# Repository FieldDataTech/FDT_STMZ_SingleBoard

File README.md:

# FDT_STMZ_SingleBoard
Single board solution for FDT smart cam using STM32H743ZIT
These are Eagle CADSoft design files for a single board implementation of FDT's smart camera. It is based on a 144-pin STM32H743ZIT processor.

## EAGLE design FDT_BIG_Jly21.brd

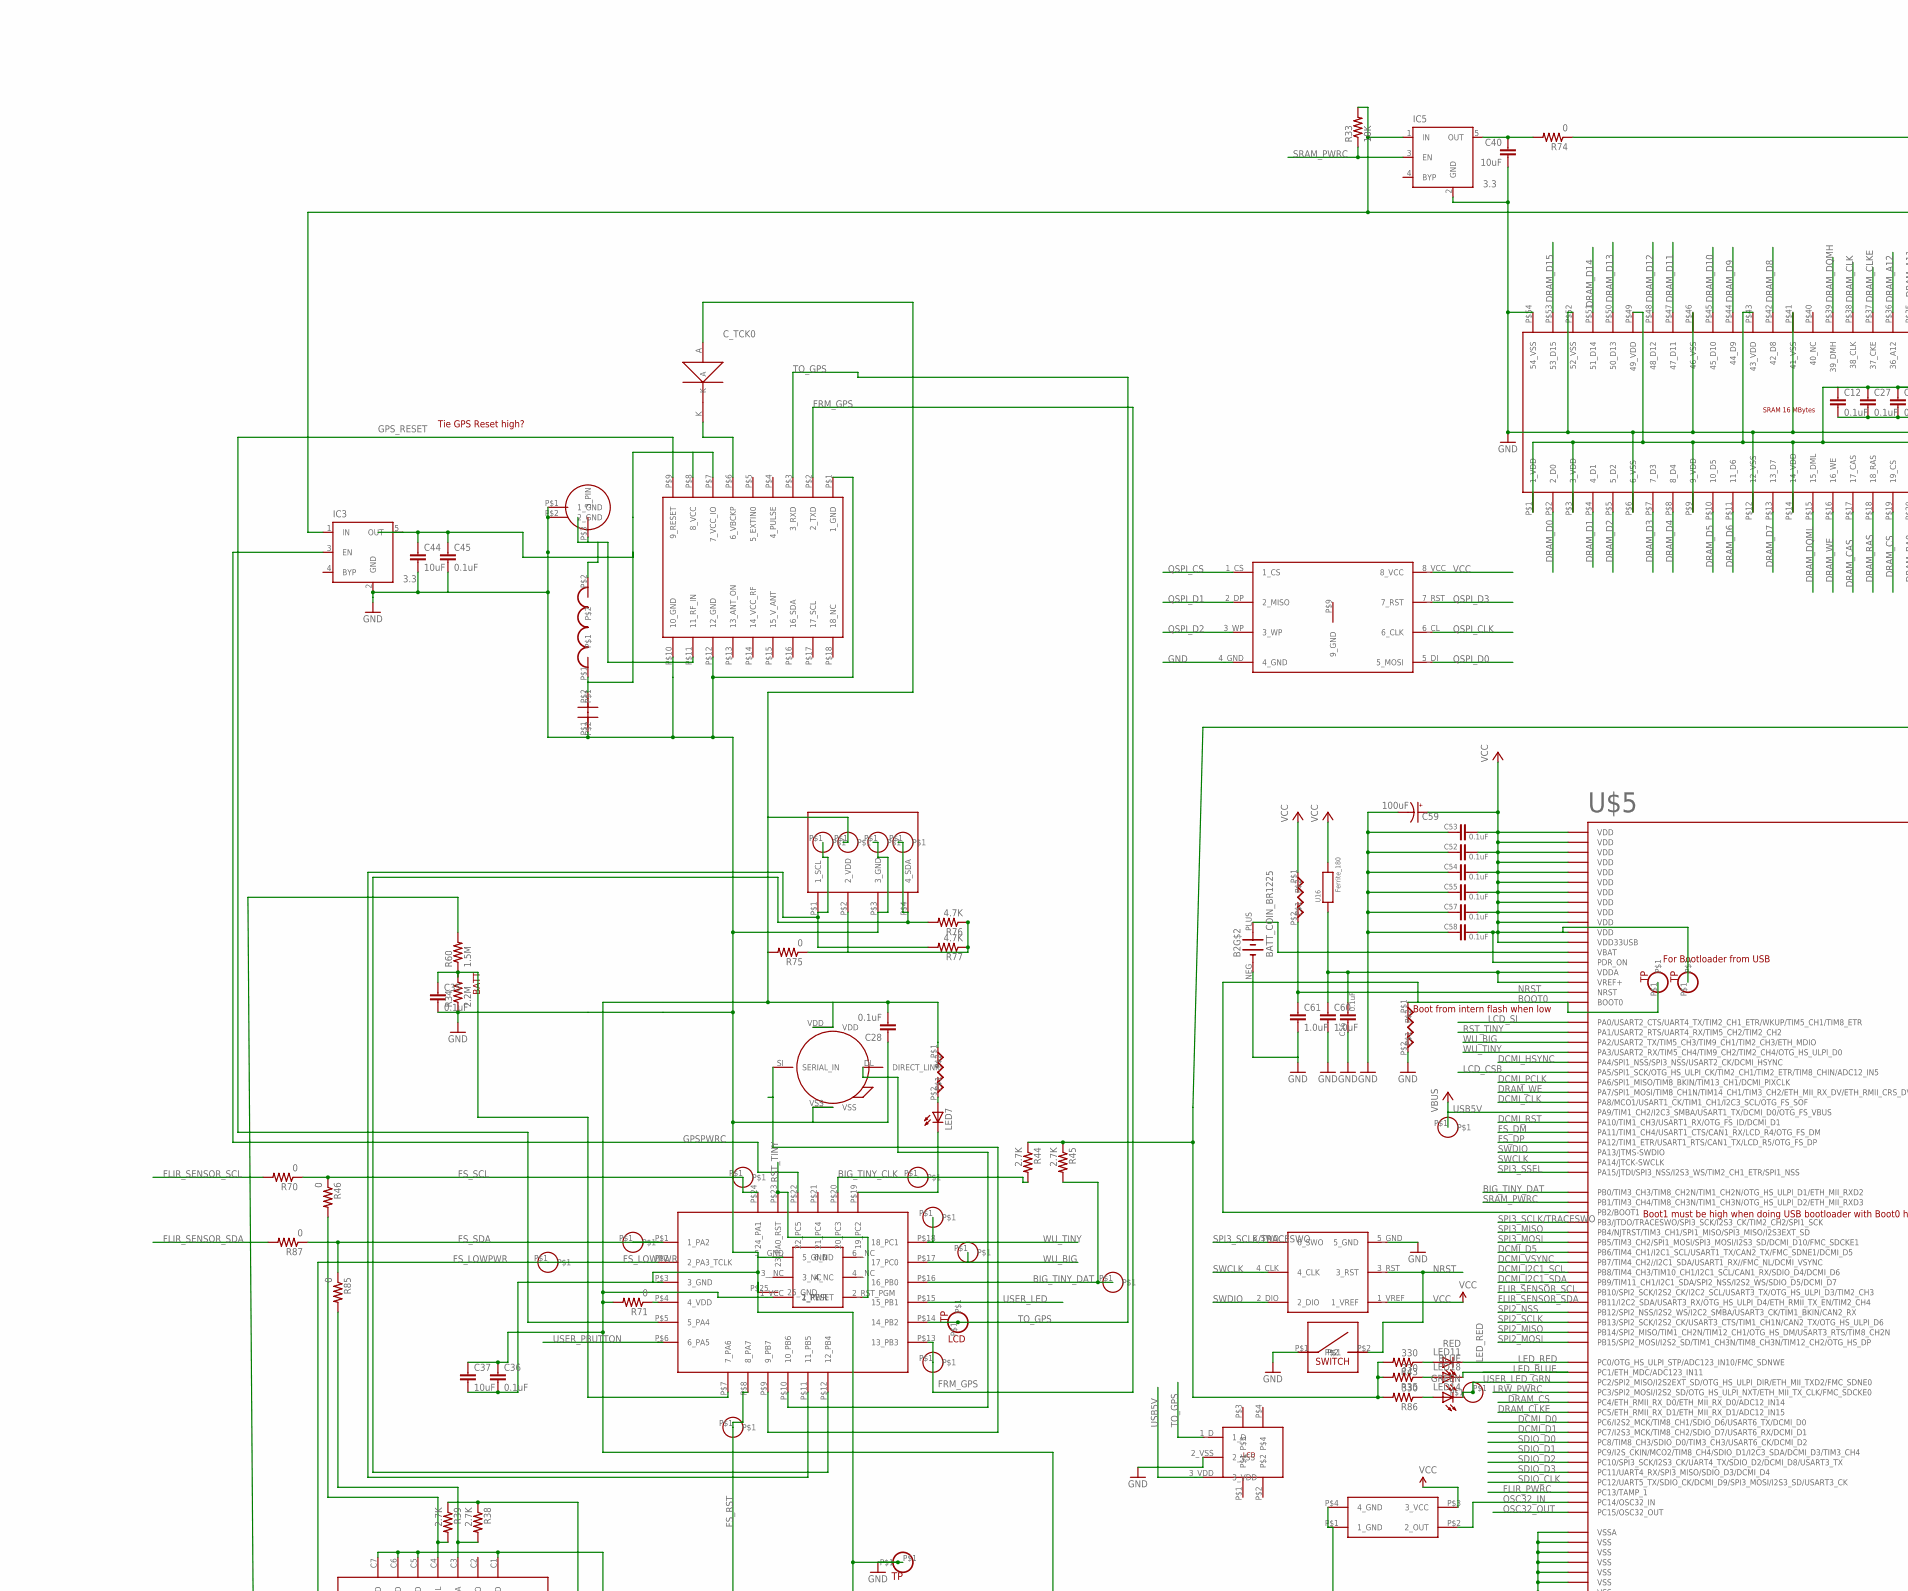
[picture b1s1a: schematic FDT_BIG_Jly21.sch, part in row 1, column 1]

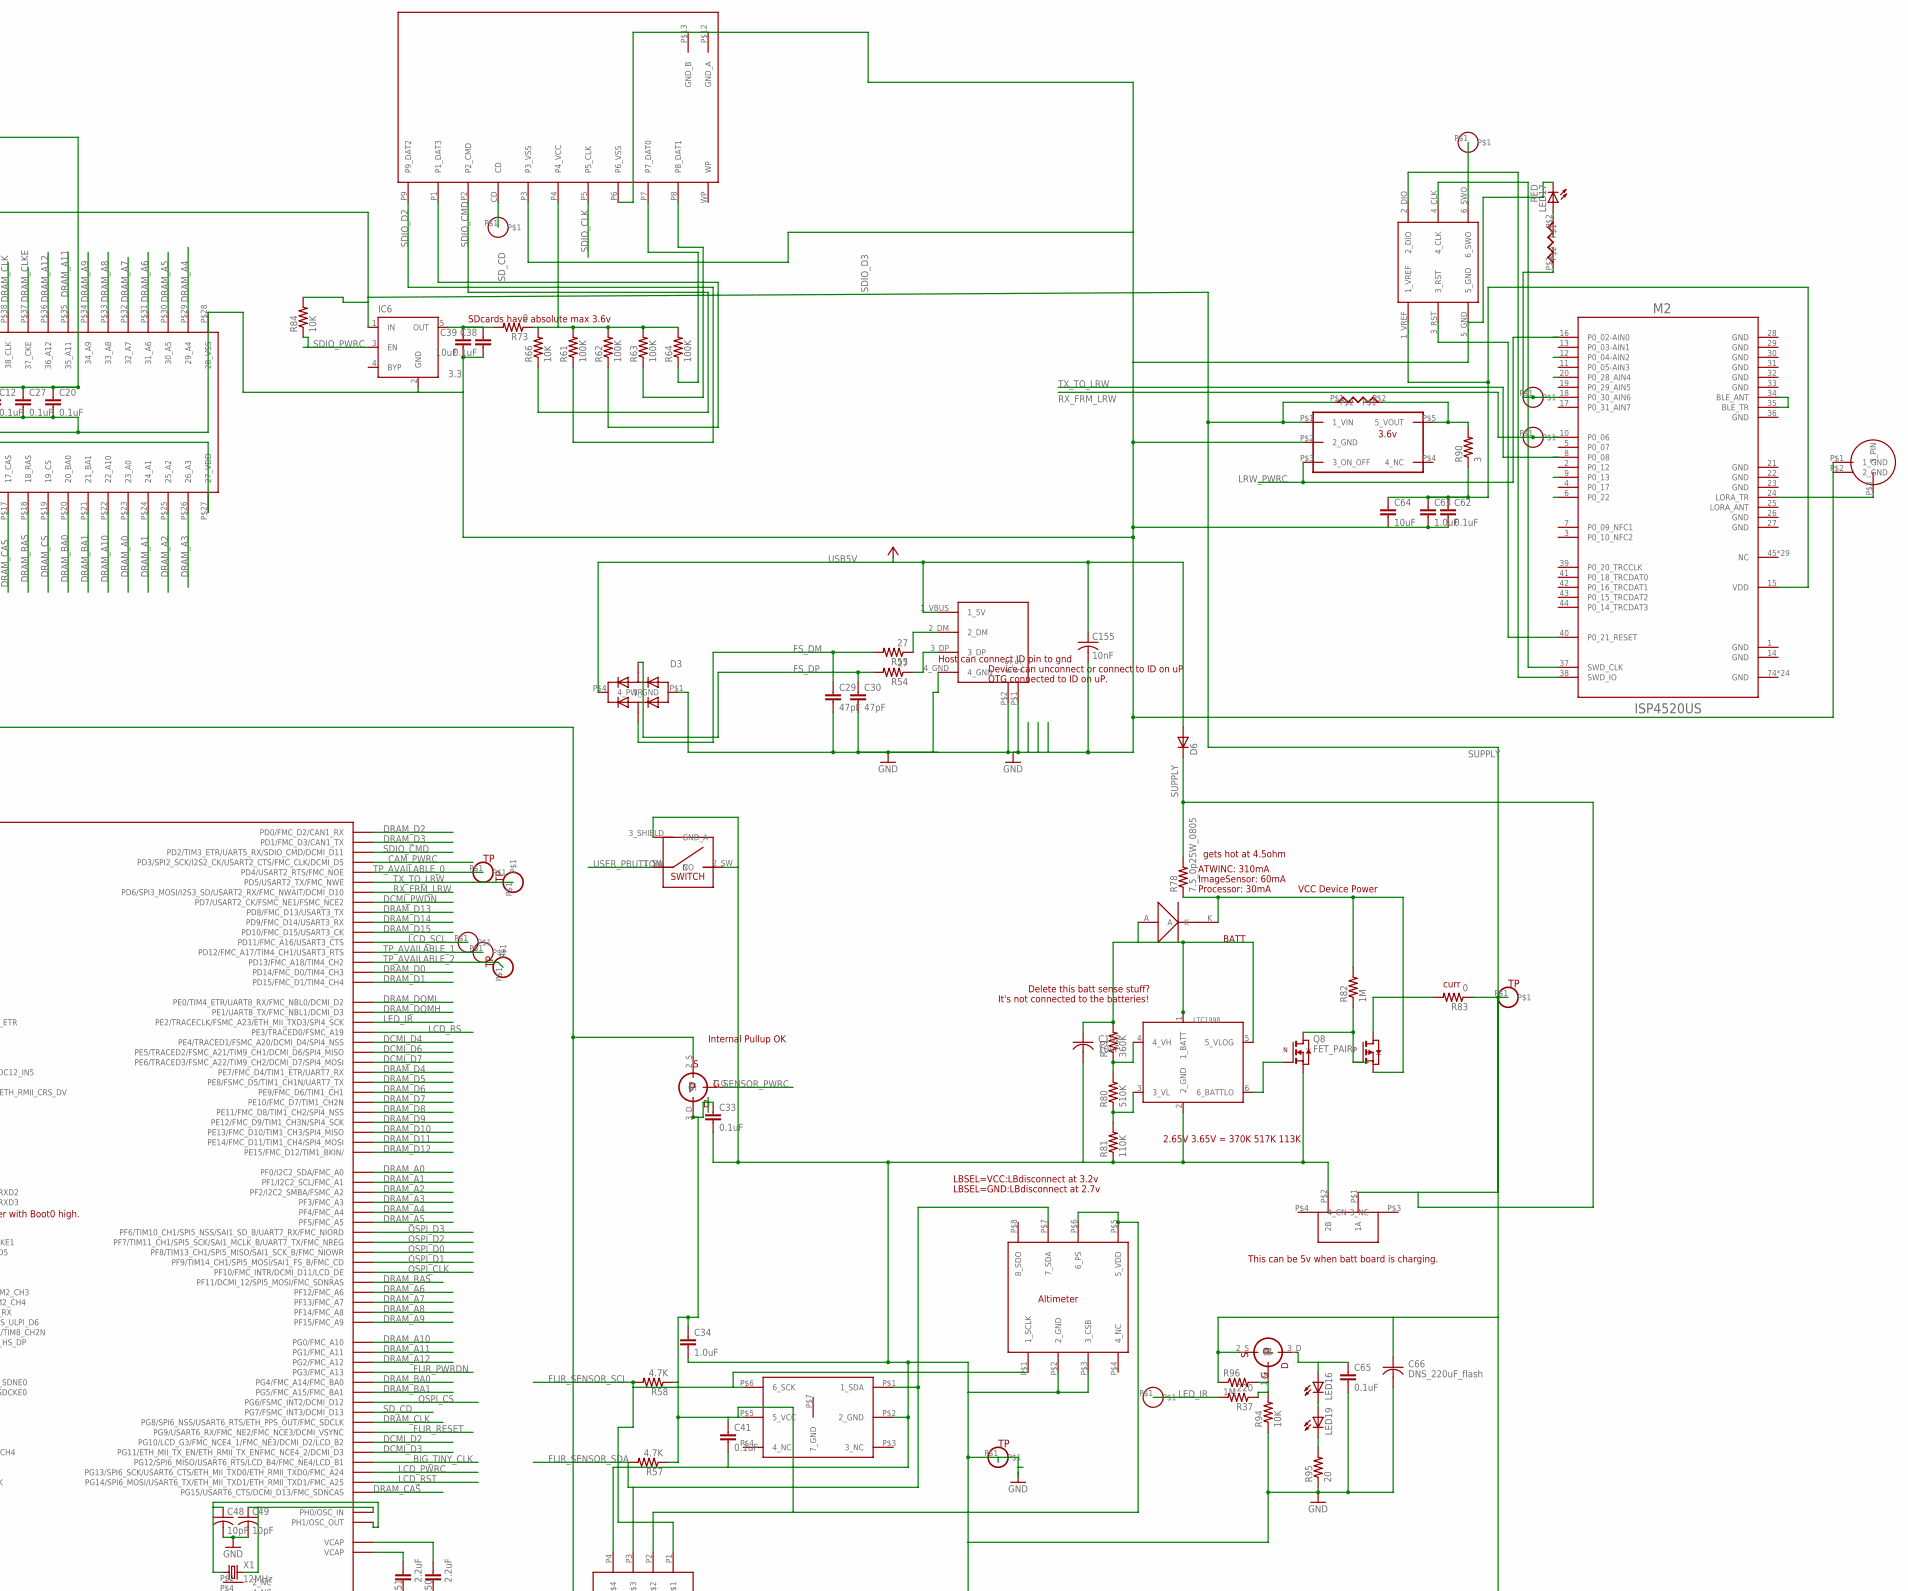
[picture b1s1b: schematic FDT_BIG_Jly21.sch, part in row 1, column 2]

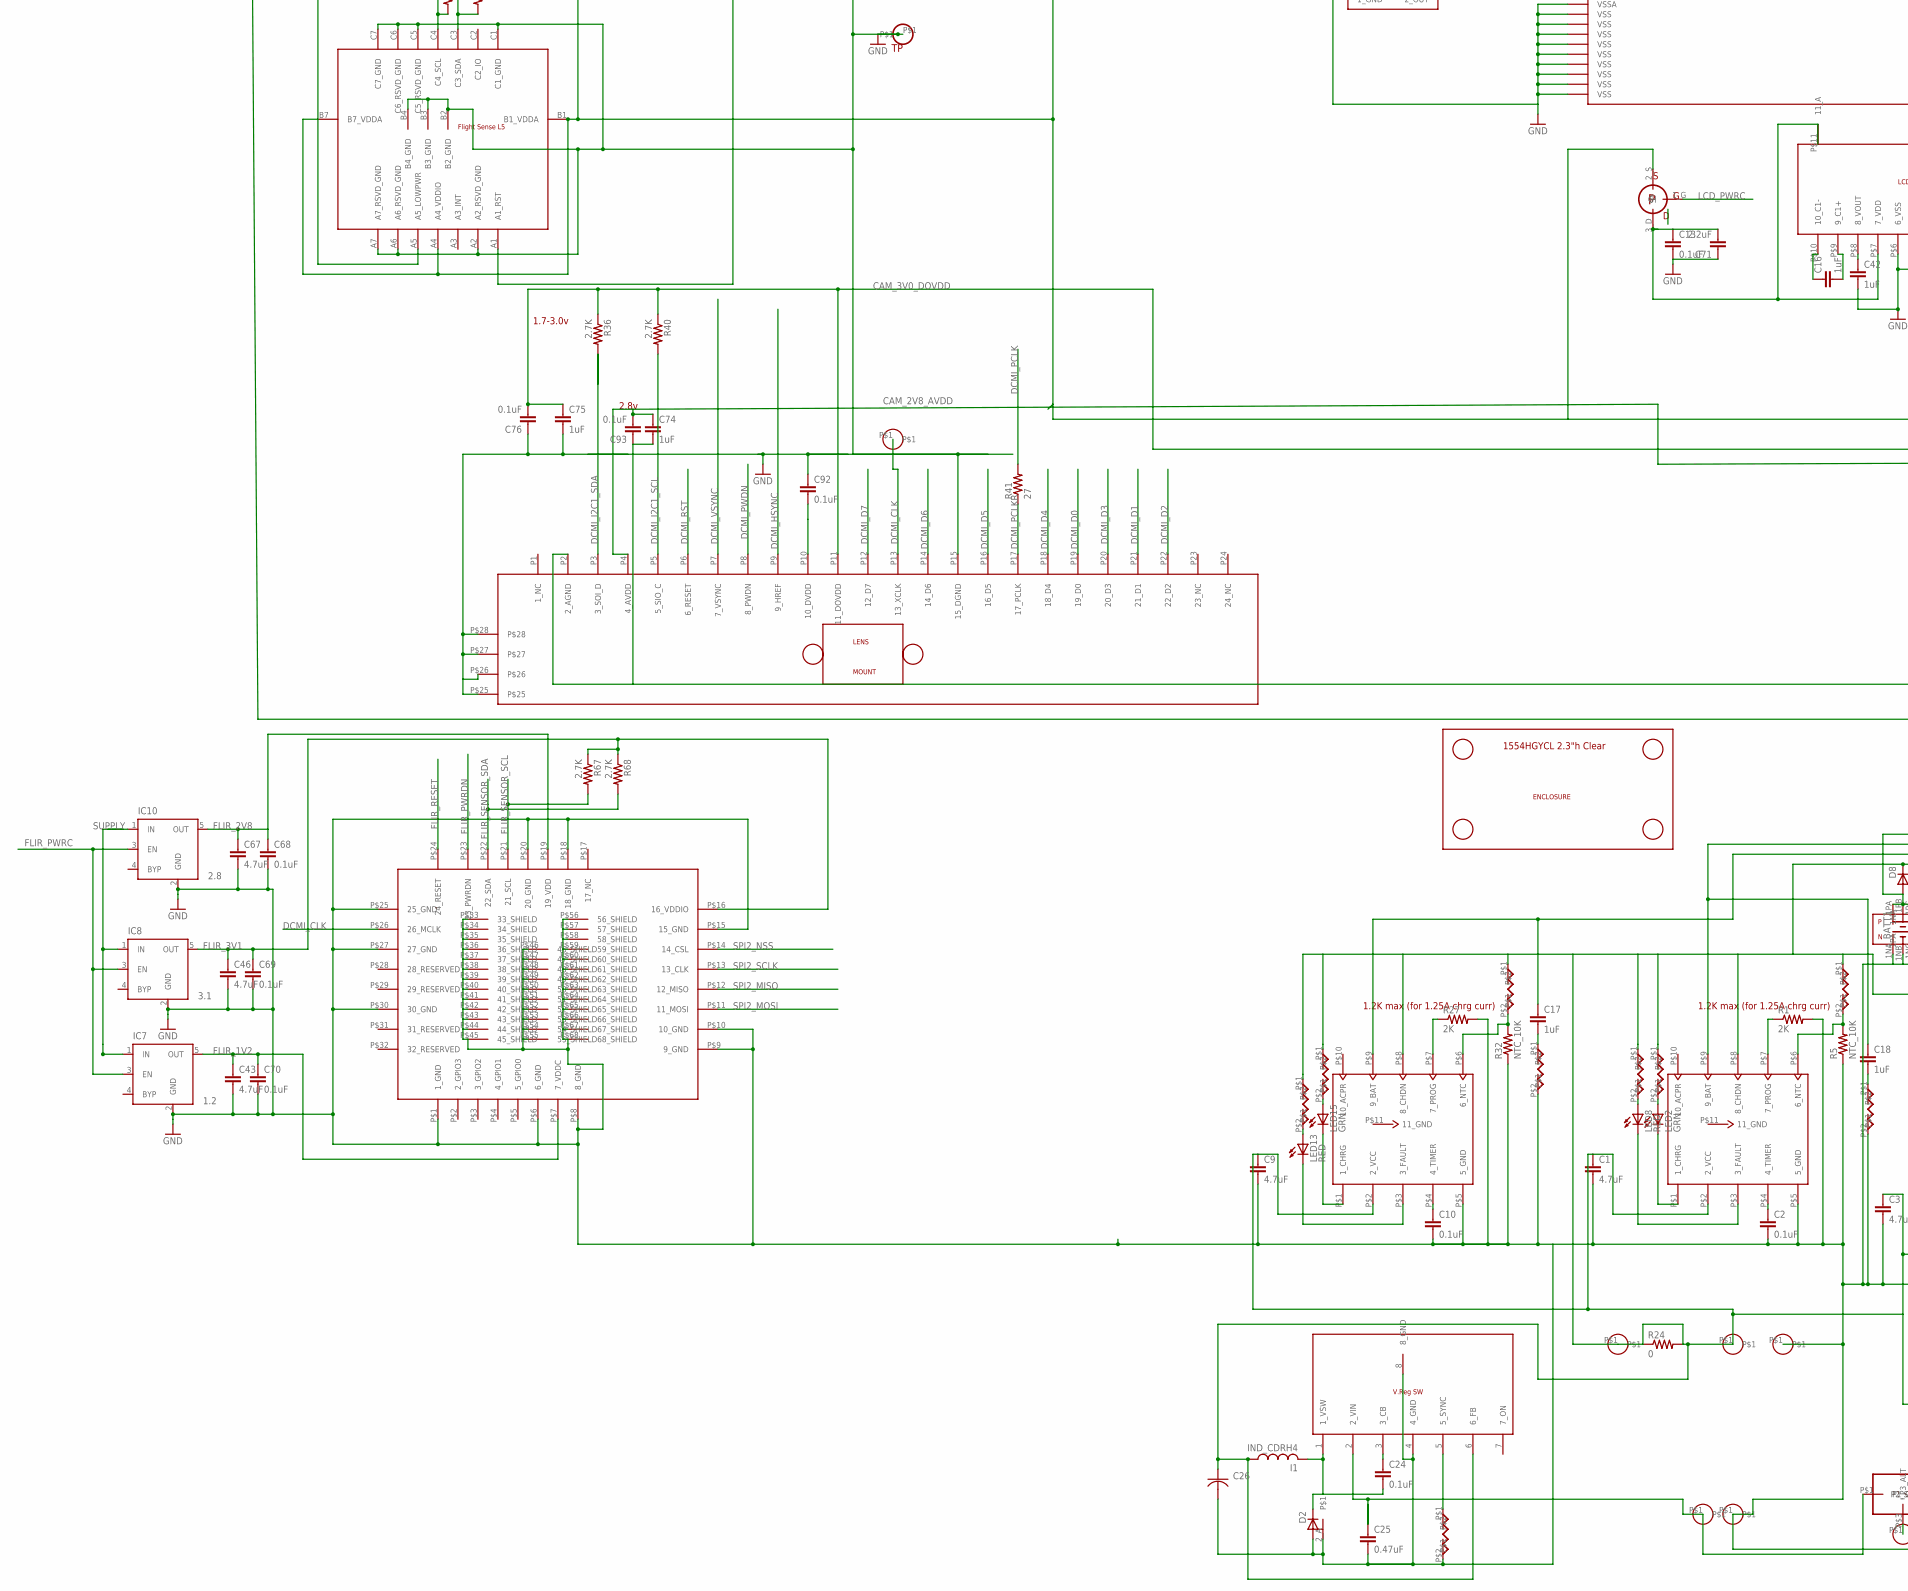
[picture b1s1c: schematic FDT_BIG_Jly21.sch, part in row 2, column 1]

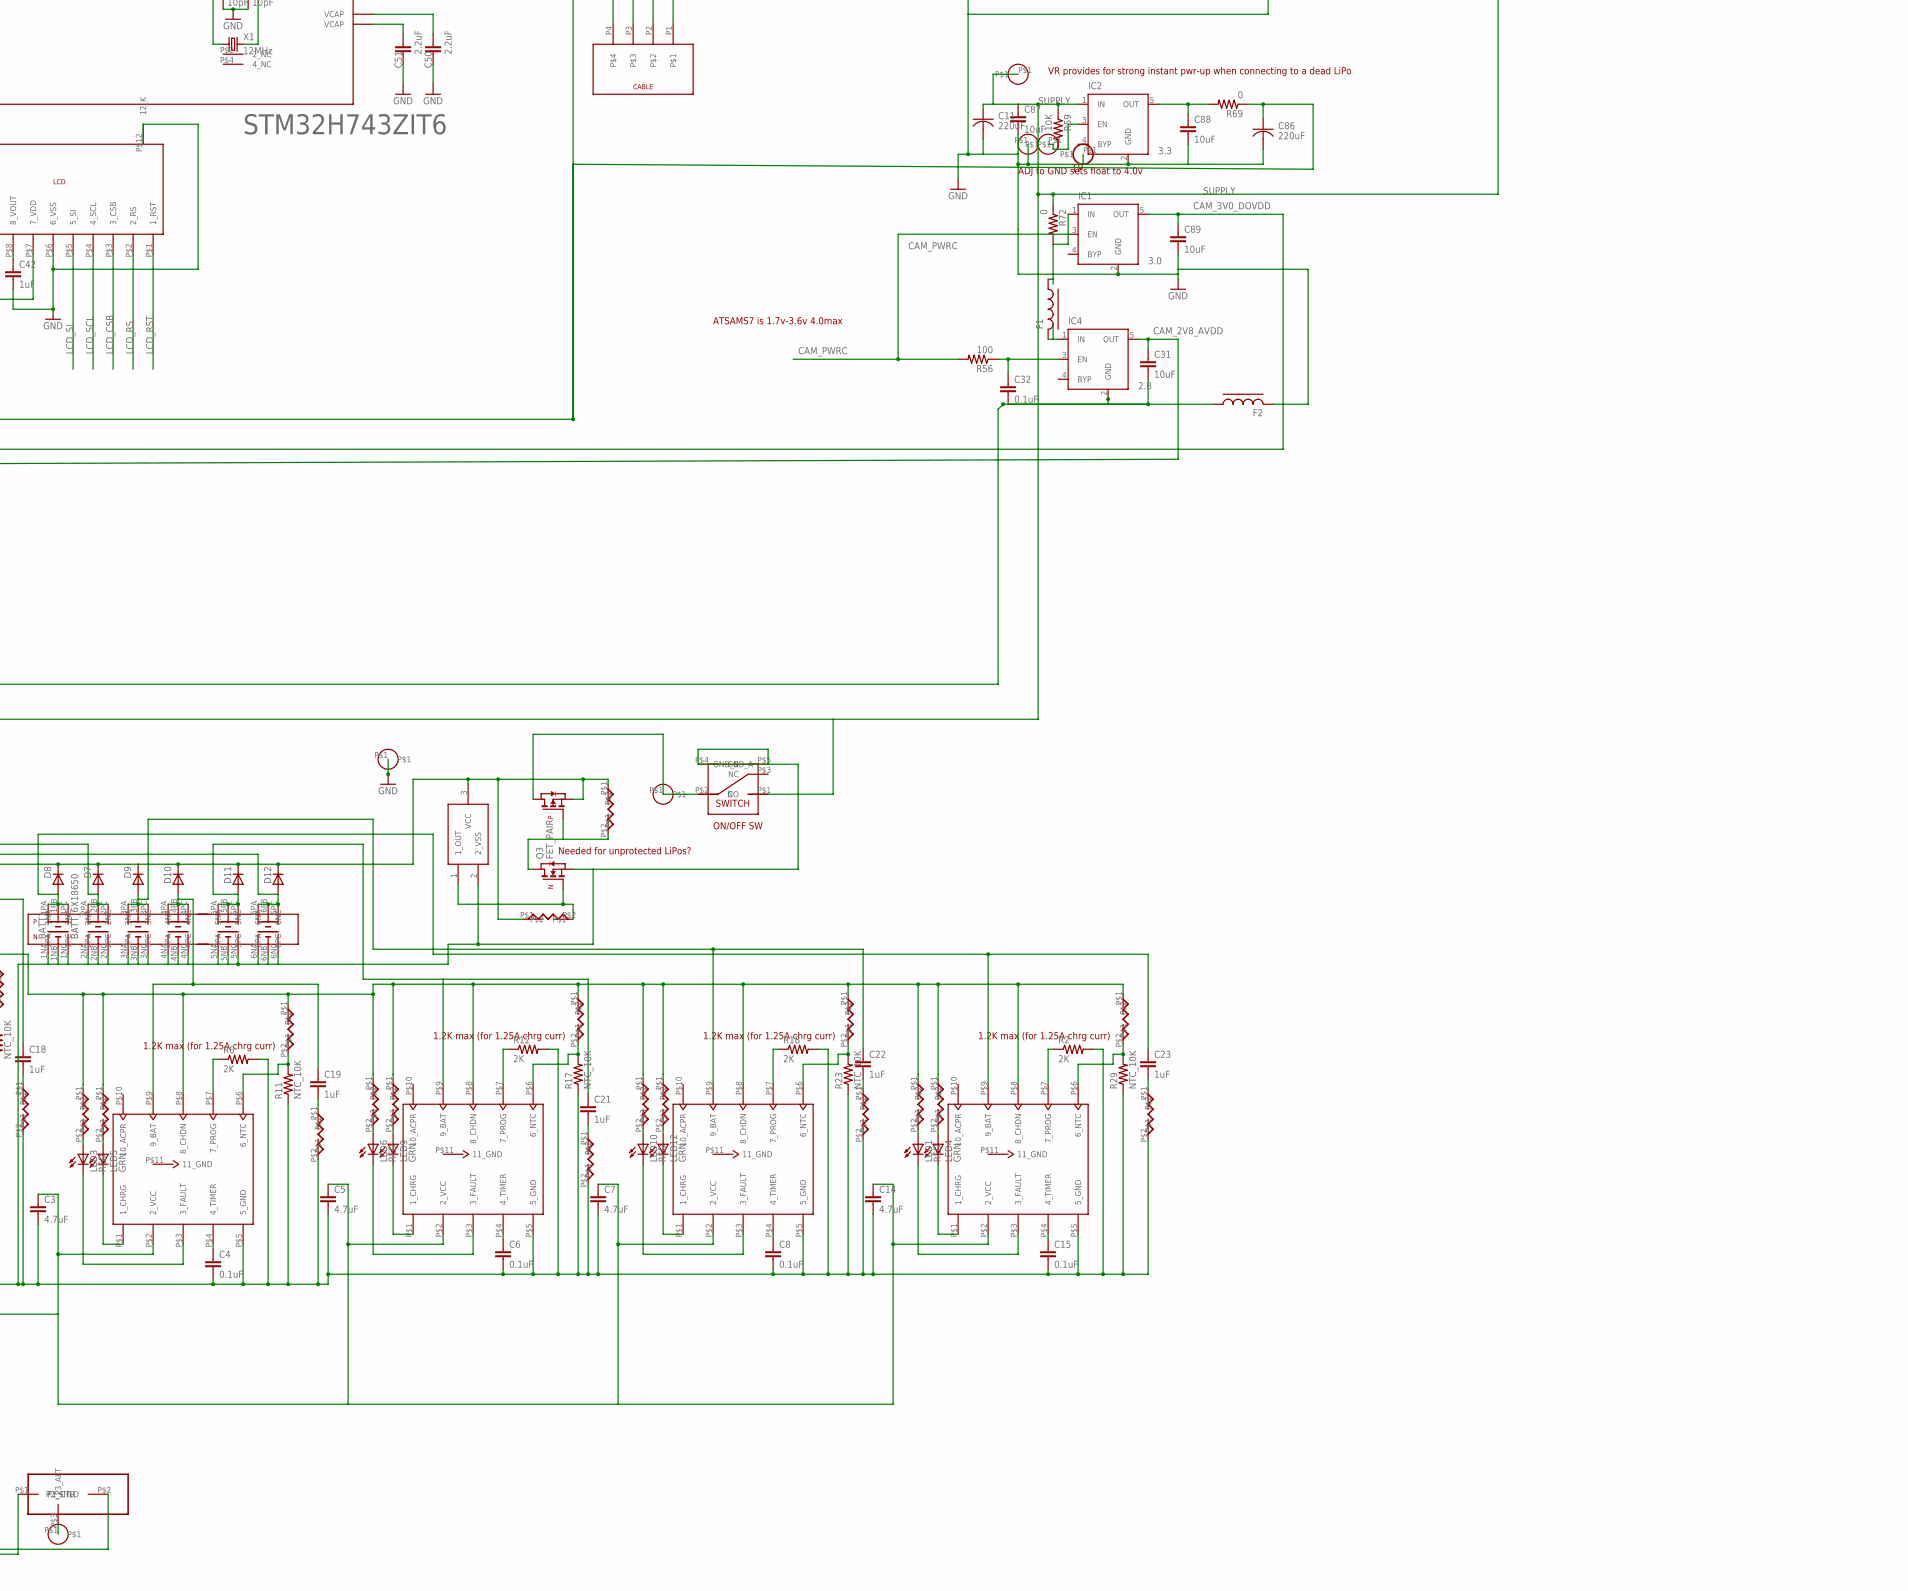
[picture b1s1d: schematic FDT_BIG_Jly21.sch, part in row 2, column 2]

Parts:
B2: BATT_COIN_BR1225
BATT1: BATT_6X18650; BATT_HALFX6
BOX1: ENCL_1554H
C1, C3, C5, C7, C9, C14, C43, C46, C67: 4.7uF; C0603
C2, C4, C6, C8, C10, C12, C13, C15, C20, C24, C27, C28, C32, C33, C35, C36, C38, C41, C45, C62, C65, C68, C69, C70, C76, C92, C93: 0.1uF; C0402
C11, C86: 220uF; C1210K
C16, C17, C18, C19, C21, C22, C23, C42, C74, C75: 1uF; C0603
C25: 0.47uF; C0402
C26: CAP_1210; C1210K
C29, C30: 47pF; C0402
C31, C37, C39, C40, C44, C64, C87, C88, C89: 10uF; C0603
C34, C60, C61, C63: 1.0uF; C0603
C47: 18pF; SMD_0402
C48, C49: 10pF; SMD_0402
C50, C51: 2.2uF; 0603-CAP
C52, C53, C54, C55, C56, C57, C58: 0.1uF; 0402-CAP
C59: 100uF; EIA3216
C66: DNS_220uF_flash; C1210K
C71: 2.2uF; C0603
C102: 10uF; C0805ELEC
C155: 10nF; SMD_0402
D2: DIODE_BIG
D3: ESD_SM; TVSDIODE
D4, D5: DIO_SCH; SOD323
D6, D7, D8, D9, D10, D11, D12: DIODE_SCHTKY; SOD323
F1, F2: FERRITE_0603; R0603
G1, G2: GPS_ANT; GPS_ANTE
I1: IND_CDRH4; IND_CDRH4D
IC1: 3.0; SOT23-5
IC2, IC3, IC5, IC6: 3.3; SOT23-5
IC4, IC10: 2.8; SOT23-5
IC7: 1.2; SOT23-5
IC8: 3.1; SOT23-5
IR1: FLIR_LEPTOP_SOCKET; FLIR_SOCKET
J2: CONN_FPC_24P; CONN_FPC_24PIN
J3: USB_B_SMT_HORIZ
J4, J8: HDR_SEGER_6P; HDR_SEGGER_6P
J5: HDR_PGM_TINY_SMT
J6: CONN_4PCABLE_VERT; CONN_4PCABLE
J7: CONN_2PCABLE_SMT
J9: PWR_JAC4
L5: 100nH; SMD_IND
LCD1: LCD_NHD_3PIN; LCD_NHD_3PINS
LED1, LED3, LED6, LED8, LED10, LED11, LED13, LED17: RED; CHIP-LED0603
LED2, LED4, LED5, LED9, LED12, LED15: GRN; CHIP-LED0603
LED7: LEDCHIP-LED0603; CHIP-LED0603
LED14: GREEN; LED_RA_SM
LED16, LED19: LED5MM
LED18: BLUE; LED_RA_SM
LM2: LENS_MOUNT_CMT107
M2: ISP4520US; ISP4520-LGA-QFN74-9.8X17.2X1.7MM
PIR2: PIR_DUAL_4P; PIR_4P
Q1, Q2, Q5: MOSFET_P; SOT23_PFET
Q3, Q8: FET_PAIR; SSOT6
R1, R2, R6, R12, R18, R27: 2K; SMD_0402
R3, R7, R8, R9, R13, R14, R15, R19, R21, R28, R30, R53, R65, R92: 1K; SMD_0402
R4, R10, R16, R20, R22, R31: 4k; SMD_0402
R5, R11, R17, R23, R29, R32: NTC_10K; R0603
R24: 0; SMD_0402
R25, R26: 1M; SMD_0402
R33, R59, R66, R84, R94: 10K; R0402
R34: 2.2M; R0402
R35, R43, R86: 330; R0402
R36, R38, R39, R40, R44, R45, R67, R68: 2.7K; SMD_0402
R37: 220; R0402
R41: 27; SMD_0402
R42: 330; SMD_0402
R46, R69, R70, R71, R72, R73, R74, R75, R83, R85, R87: 0; R0402
R47, R48, R49, R50, R51, R52: 1ohm; SMD_0402
R54, R55: 27; R0402
R56: 100; R0402
R57, R58, R76, R77: 4.7K; R0402
R60: 1.5M; R0402
R61, R62, R63, R64: 100K; R0402
R78: 7.5_0p25W_0805; M0805
R79: 360K; R0402
R80: 510K; R0402
R81: 110K; R0402
R82, R96: 1M; R0402
R88, R89: 10K; SMD_0402
R90: 3; R0402
R91: DNS_0; SMD_0402
R95: 20; R0402
SD1: SD_CARD
SW1: SWITH_NO; SW_SQ
SW2: SWITCH_TOG_RA; SW_TOG_RA
SW3: SW_PBUTTON_RA
T1, T2, T3, T4, T5, T6, T7, T8, T12, T13: TESTP_SM
TP1, TP2, TP3, TP4, TP5, TP6, TP7, TP14, TP16, TP17, TP24: TP_THSM2
TP8, TP9, TP10, TP18, TP19, TP20, TP21, TP22, TP23, TP25, TP26, TP27, TP29, TP31, TP32, TP41, TP42, TP43, TP46: TP_SMT
TP11, TP12, TP13, TP15: TP_THSM
U1, U2, U3, U4, U5, U10: LTC4053
U6: HUMIDITY_A
U7: VOLT_SUPR; TO236
U8: FLIGHTSENSE_L5; FLIGHT_SENSE_L5
U11: VREG_SW_LM2677; TO263-7
U12: SRAM_16M_2X16; TSOP_54
U13: ALS
U15: UBLOX_M8
U16: Ferrite_180; 0402-CAP
U17: FLASH_SPI; WSON_8
U18: 3.6v; SOT_235B
U19: LTC1998; SOT23-6L
U20: ALTIMETER_TEC
U24: ATTINY_817_QFN; QFN24
U$1: LCD_3V_SMALL
U$5: STM32H743ZIT6; LQFP144@1
X1: 12MHz; XTAL_SMALL
X2: TCXO_32K_BGA

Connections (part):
5VREG_OUT: C1.1, C3.1, C5.1, C7.1, C9.1, C14.1, C26.1 (1P), D7.1_K (K), D8.1_K (K), D9.1_K (K), D10.1_K (K), D11.1_K (K), D12.1_K (K), I1.P$3 (1), Q3.2 (P_S), R3.P$1, R4.P$1, R7.P$1, R8.P$1, R9.P$1, R10.P$1, R13.P$1, R14.P$1, R15.P$1, R16.P$1, R19.P$1, R20.P$1, R21.P$1, R22.P$1, R24.P$1 (1), R24.P$2 (2), R25.P$1, R26.P$1, R28.P$1, R30.P$1, R31.P$1, R65.P$1, TP2.P$1, TP4.P$1, U1.P$2 (2_VCC), U1.P$8 (8_CHDN), U2.P$2 (2_VCC), U2.P$8 (8_CHDN), U3.P$2 (2_VCC), U3.P$8 (8_CHDN), U4.P$2 (2_VCC), U4.P$8 (8_CHDN), U5.P$2 (2_VCC), U5.P$8 (8_CHDN), U7.3 (VCC), U10.P$2 (2_VCC), U10.P$8 (8_CHDN), U11.6 (6_FB)
AGND: C31.2, C32.2, C74.2, C93.1, F2.1, IC4.2 (GND), J2.P2 (2_AGND)
BATT: C102.1P, D5.A, R79.2, U19.1 (1_BATT), U19.5 (5_VLOG)
BIG_TINY_CLK: R44.P$2 (2), TP29.P$1, U24.P$20 (20_PC3), U$5.127 (PG12/SPI6_MISO/USART6_RTS/LCD_B4/FMC_NE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)
BIG_TINY_DAT: R45.P$2 (2), TP27.P$1, U24.P$16 (16_PB0), U$5.46 (PB0/TIM3_CH3/TIM8_CH2N/TIM1_CH2N/OTG_HS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)
BOOT0: R89.P$1, T7.P$1, U$5.48 (PB2/BOOT1), U$5.138 (BOOT0)
CAM_2V8_AVDD: C31.1, C74.1, C93.2, IC4.5 (OUT), J2.P4 (4_AVDD)
CAM_3V0_DOVDD: C75.1, C76.2, C89.1, IC1.5 (OUT), J2.P11 (11_DOVDD), R36.P$1 (1), R40.P$1 (1)
CAM_PWRC: IC1.3 (EN), R56.2, U$5.117 (PD3/SPI2_SCK/I2S2_CK/USART2_CTS/FMC_CLK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)
DCMI_CLK: IR1.P$26 (26_MCLK), J2.P13 (13_XCLK), TP25.P$1, U$5.100 (PA8/MCO1/USART1_CK/TIM1_CH1/I2C3_SCL/OT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)
DCMI_D0: J2.P19 (19_D0), U$5.96 (PC6/I2S2_MCK/TIM8_CH1/SDIO_D6/USART6_TX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)
DCMI_D1: J2.P21 (21_D1), U$5.97 (PC7/I2S3_MCK/TIM8_CH2/SDIO_D7/USART6_RX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)
DCMI_D2: J2.P22 (22_D2), U$5.125 (PG10/LCD_G3/FMC_NCE4_1/FMC_NE3/DCMI_D2/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)
DCMI_D3: J2.P20 (20_D3), U$5.126 (PG11/ETH_MII_TX_EN/ETH_RMII_TX_ENFMC_NC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)
DCMI_D4: J2.P18 (18_D4), U$5.3 (PE4/TRACED1/FSMC_A20/DCMI_D4/SPI4_NSS)
DCMI_D5: J2.P16 (16_D5), U$5.136 (PB6/TIM4_CH1/I2C1_SCL/USART1_TX/CAN2_TX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)
DCMI_D6: J2.P14 (14_D6), U$5.4 (PE5/TRACED2/FSMC_A21/TIM9_CH1/DCMI_D6/S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)
DCMI_D7: J2.P12 (12_D7), U$5.5 (PE6/TRACED3/FSMC_A22/TIM9_CH2/DCMI_D7/S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)
DCMI_HSYNC: J2.P9 (9_HREF), U$5.40 (PA4/SPI1_NSS/SPI3_NSS/USART2_CK/DCMI_HS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)
DCMI_I2C1_SCL: J2.P5 (5_SIO_C), R40.P$2 (2), U$5.139 (PB8/TIM4_CH3/TIM10_CH1/I2C1_SCL/CAN1_RX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)
DCMI_I2C1_SDA: J2.P3 (3_SOI_D), R36.P$2 (2), U$5.140 (PB9/TIM11_CH1/I2C1_SDA/SPI2_NSS/I2S2_WS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)
DCMI_PCLK: R41.P$2 (2), U$5.42 (PA6/SPI1_MISO/TIM8_BKIN/TIM13_CH1/DCMI_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)
DCMI_PCLKR: J2.P17 (17_PCLK), R41.P$1 (1)
DCMI_PWDN: J2.P8 (8_PWDN), U$5.123 (PD7/USART2_CK/FSMC_NE1/FSMC_NCE2)
DCMI_RST: J2.P6 (6_RESET), U$5.102 (PA10/TIM1_CH3/USART1_RX/OTG_FS_ID/DCMI_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)
DCMI_VSYNC: J2.P7 (7_VSYNC), U$5.137 (PB7/TIM4_CH2//I2C1_SDA/USART1_RX//FMC_N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)
DISABLE_PWR: IC2.3 (EN), R59.2, TP17.P$1
DRAM_A0: U12.P$23 (23_A0), U$5.10 (PF0/I2C2_SDA/FMC_A0)
DRAM_A1: U12.P$24 (24_A1), U$5.11 (PF1/I2C2_SCL/FMC_A1)
DRAM_A2: U12.P$25 (25_A2), U$5.12 (PF2/I2C2_SMBA/FSMC_A2)
DRAM_A3: U12.P$26 (26_A3), U$5.13 (PF3/FMC_A3)
DRAM_A4: U12.P$29 (29_A4), U$5.14 (PF4/FMC_A4)
DRAM_A5: U12.P$30 (30_A5), U$5.15 (PF5/FMC_A5)
DRAM_A6: U12.P$31 (31_A6), U$5.50 (PF12/FMC_A6)
DRAM_A7: U12.P$32 (32_A7), U$5.53 (PF13/FMC_A7)
DRAM_A8: U12.P$33 (33_A8), U$5.54 (PF14/FMC_A8)
DRAM_A9: U12.P$34 (34_A9), U$5.55 (PF15/FMC_A9)
DRAM_A10: U12.P$22 (22_A10), U$5.56 (PG0/FMC_A10)
DRAM_A11: U12.P$35 (35_A11), U$5.57 (PG1/FMC_A11)
DRAM_A12: U12.P$36 (36_A12), U$5.87 (PG2/FMC_A12)
DRAM_BA0: U12.P$20 (20_BA0), U$5.89 (PG4/FMC_A14/FMC_BA0)
DRAM_BA1: U12.P$21 (21_BA1), U$5.90 (PG5/FMC_A15/FMC_BA1)
DRAM_CAS: U12.P$17 (17_CAS), U$5.132 (PG15/USART6_CTS/DCMI_D13/FMC_SDNCAS)
DRAM_CLK: U12.P$38 (38_CLK), U$5.93 (PG8/SPI6_NSS/USART6_RTS/ETH_PPS_OUT/FMC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)
DRAM_CLKE: U12.P$37 (37_CKE), U$5.45 (PC5/ETH_RMII_RX_D1/ETH_MII_RX_D1/ADC12_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)
DRAM_CS: U12.P$19 (19_CS), U$5.44 (PC4/ETH_RMII_RX_D0/ETH_MII_RX_D0/ADC12_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)
DRAM_D0: U12.P$2 (2_D0), U$5.85 (PD14/FMC_D0/TIM4_CH3)
DRAM_D1: U12.P$4 (4_D1), U$5.86 (PD15/FMC_D1/TIM4_CH4)
DRAM_D2: U12.P$5 (5_D2), U$5.114 (PD0/FMC_D2/CAN1_RX)
DRAM_D3: U12.P$7 (7_D3), U$5.115 (PD1/FMC_D3/CAN1_TX)
DRAM_D4: U12.P$8 (8_D4), U$5.58 (PE7/FMC_D4/TIM1_ETR/UART7_RX)
DRAM_D5: U12.P$10 (10_D5), U$5.59 (PE8/FSMC_D5/TIM1_CH1N/UART7_TX)
DRAM_D6: U12.P$11 (11_D6), U$5.60 (PE9/FMC_D6/TIM1_CH1)
DRAM_D7: U12.P$13 (13_D7), U$5.63 (PE10/FMC_D7/TIM1_CH2N)
DRAM_D8: U12.P$42 (42_D8), U$5.64 (PE11/FMC_D8/TIM1_CH2/SPI4_NSS)
DRAM_D9: U12.P$44 (44_D9), U$5.65 (PE12/FMC_D9/TIM1_CH3N/SPI4_SCK)
DRAM_D10: U12.P$45 (45_D10), U$5.66 (PE13/FMC_D10/TIM1_CH3/SPI4_MISO)
DRAM_D11: U12.P$47 (47_D11), U$5.67 (PE14/FMC_D11/TIM1_CH4/SPI4_MOSI)
DRAM_D12: U12.P$48 (48_D12), U$5.68 (PE15/FMC_D12/TIM1_BKIN/)
DRAM_D13: U12.P$50 (50_D13), U$5.77 (PD8/FMC_D13/USART3_TX)
DRAM_D14: U12.P$51 (51_D14), U$5.78 (PD9/FMC_D14/USART3_RX)
DRAM_D15: U12.P$53 (53_D15), U$5.79 (PD10/FMC_D15/USART3_CK)
DRAM_DQMH: U12.P$39 (39_DMH), U$5.142 (PE1/UART8_TX/FMC_NBL1/DCMI_D3)
DRAM_DQML: U12.P$15 (15_DML), U$5.141 (PE0/TIM4_ETR/UART8_RX/FMC_NBL0/DCMI_D2)
DRAM_RAS: U12.P$18 (18_RAS), U$5.49 (PF11/DCMI_12/SPI5_MOSI/FMC_SDNRAS)
DRAM_WE: U12.P$16 (16_WE), U$5.43 (PA7/SPI1_MOSI/TIM8_CH1N/TIM14_CH1/TIM3_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)
DVDD_REF: C92.2, J2.P10 (10_DVDD)
FLIR_1V2: C43.1, C70.1, IC7.5 (OUT), IR1.P$7 (7_VDDC)
FLIR_2V8: C67.1, C68.1, IC10.5 (OUT), IR1.P$19 (19_VDD)
FLIR_3V1: C46.1, C69.1, IC8.5 (OUT), IR1.P$16 (16_VDDIO), R67.P$1 (1), R68.P$1 (1)
FLIR_PWRC: IC7.3 (EN), IC8.3 (EN), IC10.3 (EN), U$5.7 (PC13/TAMP_1)
FLIR_PWRDN: IR1.P$23 (23_PWRDN), U$5.88 (PG3/FMC_A13)
FLIR_RESET: IR1.P$24 (24_RESET), U$5.124 (PG9/USART6_RX/FMC_NE2/FMC_NCE3/DCMI_VSY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)
FLIR_SENSOR_SCL: IR1.P$21 (21_SCL), J6.P1, R58.2, R67.P$2 (2), R70.2, U6.P$6 (6_SCK), U20.P$1 (1_SCLK), U$5.69 (PB10/SPI2_SCK/I2S2_CK/I2C2_SCL/USART3_T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)
FLIR_SENSOR_SDA: IR1.P$22 (22_SDA), J6.P3, R57.2, R68.P$2 (2), R87.2, U6.P$1 (1_SDA), U20.P$7 (7_SDA), U$5.70 (PB11/I2C2_SDA/USART3_RX/OTG_HS_ULPI_D4/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)
FRM_GPS: TP10.P$1, U15.P$2 (2_TXD), U24.P$13 (13_PB3)
FS_DM: C29.1, D3.P$2 (2_S2), R55.2, U$5.103 (PA11/TIM1_CH4/USART1_CTS/CAN1_RX/LCD_R4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)
FS_DP: C30.1, D3.P$3 (3_S1), R54.2, U$5.104 (PA12/TIM1_ETR/USART1_RTS/CAN1_TX/LCD_R5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)
FS_LOWPWR: TP43.P$1, U8.A5 (A5_LOWPWR), U24.P$2 (2_PA3_TCLK)
FS_RST: TP41.P$1, U8.A1 (A1_RST), U24.P$8 (8_PA7)
FS_SCL: R46.1, R70.1, TP42.P$1, U24.P$24 (24_PA1)
FS_SDA: R85.1, R87.1, TP9.P$1, U24.P$1 (1_PA2)
GND: B2.NEG (-), BATT1.1NA, BATT1.1NB, BATT1.1NC, BATT1.2NA, BATT1.2NB, BATT1.2NC, BATT1.3NA, BATT1.3NB, BATT1.3NC, BATT1.4NA, BATT1.4NB, BATT1.4NC, BATT1.5NA, BATT1.5NB, BATT1.5NC, BATT1.6NA, BATT1.6NB, BATT1.6NC, C1.2, C2.2, C3.2, C4.2, C5.2, C6.2, C7.2, C8.2, C9.2, C10.2, C11.2 (2N), C12.2, C13.2, C14.2, C15.2, C20.2, C25.2, C26.2 (2N), C27.2, C28.1, C29.2, C30.2, C33.2, C34.2, C35.2, C36.2, C37.2, C38.2, C39.2, C40.2, C41.2, C42.2, C43.2, C44.2, C45.2, C46.2, C47.P$1, C48.P$2 (2), C49.P$2 (2), C50.2, C51.2, C52.2, C53.2, C54.2, C55.2, C56.2, C57.2, C58.2, C59.C (-), C60.2, C61.2, C62.2, C63.2, C64.2, C65.2, C66.2 (2N), C67.2, C68.2, C69.2, C70.2, C71.1, C75.2, C76.1, C86.2 (2N), C87.2, C88.2, C89.2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
GPS1: G2.P$3 (3_PIN), L5.P$2, U15.P$11 (11_RF_IN)
GPSPWRC: IC3.3 (EN), U24.P$22 (22_PC5)
GPS_RESET: U15.P$9 (9_RESET), U24.P$5 (5_PA4)
GPS_VCC_X: C44.1, C45.1, C47.P$2, IC3.5 (OUT), L5.P$1, U15.P$7 (7_VCC_IO), U15.P$8 (8_VCC)
LCD_CSB: U$1.P$3 (3_CSB), U$5.41 (PA5/SPI1_SCK/OTG_HS_ULPI_CK/TIM2_CH1/TI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)
LCD_PWRC: Q2.1_G (G), U$5.128 (PG13/SPI6_SCK/USART6_CTS/ETH_MII_TXD0/E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)
LCD_RS: U$1.P$2 (2_RS), U$5.2 (PE3/TRACED0/FSMC_A19)
LCD_RST: U$1.P$1 (1_RST), U$5.129 (PG14/SPI6_MOSI/USART6_TX/ETH_MII_TXD1/E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)
LCD_SCL: TP21.P$1, U$1.P$4 (4_SCL), U$5.80 (PD11/FMC_A16/USART3_CTS)
LCD_SI: U$1.P$5 (5_SI), U$5.34 (PA0/USART2_CTS/UART4_TX/TIM2_CH1_ETR/WK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)
LED_BLUE: LED18.2_K (C), U$5.27 (PC1/ETH_MDC/ADC123_IN11)
LED_IR: R37.2, TP46.P$1, U$5.1 (PE2/TRACECLK/FSMC_A23/ETH_MII_TXD3/SPI4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)
LED_RED: LED11.C, U$5.26 (PC0/OTG_HS_ULPI_STP/ADC123_IN10/FMC_SDN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)
LORA_ANT: M2.25 (LORA_ANT)
LRW_PWRC: M2.16 (P0_02-AIN0), U18.P$3 (3_ON_OFF), U$5.29 (PC3/SPI2_MOSI/I2S2_SD/OTG_HS_ULPI_NXT/E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)
unnamed: R53.P$1, U11.5 (5_SYNC)
unnamed: BATT1.6PA, BATT1.6PB, BATT1.6PC, C17.1, D12.2_A (A), U2.P$9 (9_BAT)
unnamed: C15.1, U10.P$4 (4_TIMER)
unnamed: R2.P$1 (1), U10.P$7 (7_PROG)
unnamed: LED1.A, R8.P$2
unnamed: Q3.4 (P_D), SW2.P$2 (C), TP7.P$1
unnamed: BATT1.4PA, BATT1.4PB, BATT1.4PC, C19.1, D10.2_A (A), U3.P$9 (9_BAT)
unnamed: Q3.1 (N_G), R26.P$2, U7.1 (1_OUT)
unnamed: Q1.1_G (G), R37.1, R94.2, R96.2
unnamed: C24.1, U11.3 (3_CB)
unnamed: LED18.1_A (A), R35.1
unnamed: Q3.3 (P_G), Q3.6 (N_D), R25.P$2
unnamed: BATT1.1PA, BATT1.1PB, BATT1.1PC, C23.1, D8.2_A (A), U10.P$9 (9_BAT)
unnamed: BATT1.2PA, BATT1.2PB, BATT1.2PC, C18.1, D7.2_A (A), U1.P$9 (9_BAT)
unnamed: BATT1.5PA, BATT1.5PB, BATT1.5PC, C21.1, D11.2_A (A), U4.P$9 (9_BAT)
unnamed: J9.P$3 (P3_ALT), TP5.P$1
unnamed: C2.1, U1.P$4 (4_TIMER)
unnamed: LED4.A, R14.P$2
unnamed: R1.P$1 (1), U1.P$7 (7_PROG)
unnamed: LED2.A, R3.P$2
unnamed: LED4.C, U10.P$1 (1_CHRG)
unnamed: LED2.C, U1.P$1 (1_CHRG)
unnamed: LED8.C, U1.P$3 (3_FAULT)
unnamed: R4.P$2, R5.2, U1.P$6 (6_NTC)
unnamed: LED11.A, R43.1
unnamed: LED1.C, U10.P$3 (3_FAULT)
unnamed: C4.1, U3.P$4 (4_TIMER)
unnamed: R6.P$1 (1), U3.P$7 (7_PROG)
unnamed: LED3.A, R7.P$2
unnamed: R20.P$2, R29.2, U10.P$6 (6_NTC)
unnamed: LED5.A, R9.P$2
unnamed: C17.2, R47.P$1
unnamed: LED5.C, U3.P$1 (1_CHRG)
unnamed: LED3.C, U3.P$3 (3_FAULT)
unnamed: R10.P$2, R11.2, U3.P$6 (6_NTC)
unnamed: LED7.C, U24.P$19 (19_PC2)
unnamed: C10.1, U2.P$4 (4_TIMER)
unnamed: C6.1, U4.P$4 (4_TIMER)
unnamed: R12.P$1 (1), U4.P$7 (7_PROG)
unnamed: LED6.A, R13.P$2
unnamed: LED16.K (C), LED19.A
unnamed: LED9.A, R15.P$2
unnamed: LED7.A, R42.P$2
unnamed: LED9.C, U4.P$1 (1_CHRG)
unnamed: LED6.C, U4.P$3 (3_FAULT)
unnamed: R16.P$2, R17.2, U4.P$6 (6_NTC)
unnamed: C35.1, R34.2, R60.1, U24.P$7 (7_PA6)
unnamed: R27.P$1 (1), U2.P$7 (7_PROG)
unnamed: LED13.A, R28.P$2
unnamed: C8.1, U5.P$4 (4_TIMER)
unnamed: R18.P$1 (1), U5.P$7 (7_PROG)
unnamed: LED10.A, R19.P$2
unnamed: C18.2, R48.P$1
unnamed: LED12.A, R21.P$2
unnamed: C19.2, R49.P$1
unnamed: LED12.C, U5.P$1 (1_CHRG)
unnamed: LED10.C, U5.P$3 (3_FAULT)
unnamed: R22.P$2, R23.2, U5.P$6 (6_NTC)
unnamed: C32.1, IC4.3 (EN), R56.1
unnamed: LED15.A, R30.P$2
unnamed: LED15.C, U2.P$1 (1_CHRG)
unnamed: LED13.C, U2.P$3 (3_FAULT)
unnamed: R31.P$2, R32.2, U2.P$6 (6_NTC)
unnamed: C21.2, R50.P$1
unnamed: BATT1.3PA, BATT1.3PB, BATT1.3PC, C22.1, D9.2_A (A), U5.P$9 (9_BAT)
unnamed: LED19.K (C), R95.2
unnamed: B2.PLUS (+), U$5.6 (VBAT)
unnamed: R61.2, R62.2, R63.2, R64.2, R66.2, R73.1, SD1.P4 (P4_VCC)
unnamed: C13.1, C71.2, Q2.3_D (D), U$1.P$7 (7_VDD), U$1.P$11 (11_A)
unnamed: J3.2_DM, R55.1
unnamed: R39.P$2 (2), R46.2, U8.C4 (C4_SCL)
unnamed: C16.1, U$1.P$10 (10_C1-)
unnamed: C16.2, U$1.P$9 (9_C1+)
unnamed: LED8.A, R65.P$2
unnamed: J3.3_DP, R54.1
unnamed: D4.K, U15.P$6 (6_VBCKP)
unnamed: R38.P$2 (2), R85.2, U8.C3 (C3_SDA)
unnamed: C42.1, U$1.P$8 (8_VOUT)
unnamed: C22.2, R51.P$1
unnamed: R71.1, U24.P$4 (4_VDD)
unnamed: F1.1, IC1.1 (IN), R72.2
unnamed: C38.1, C39.1, IC6.5 (OUT), R73.2
unnamed: C40.1, IC5.5 (OUT), R74.2
unnamed: R79.1, R80.2, U19.4 (4_VH)
unnamed: C88.1, IC2.5 (OUT), R69.2
unnamed: C23.2, R52.P$1
unnamed: C24.2, D2.3_K (K), I1.P$4 (2), U11.1 (1_VSW)
unnamed: C25.1, J9.P$1 (P1_CTR), TP14.P$1, U11.2 (2_VIN)
unnamed: LED14.1_A (A), R86.1
unnamed: F1.2, IC4.1 (IN)
unnamed: PIR2.SI (SERIAL_IN), U24.P$9 (9_PB7)
unnamed: C48.P$1 (1), U$5.24 (PH1/OSC_OUT), X1.P$1 (1_XTAL)
unnamed: C49.P$1 (1), U$5.23 (PH0/OSC_IN), X1.P$3 (3_XTAL)
unnamed: C56.1, C60.1, U16.1, U$5.32 (VREF+), U$5.33 (VDDA)
unnamed: M2.34 (BLE_ANT), M2.35 (BLE_TR)
unnamed: J8.3_RST, M2.40 (P0_21_RESET)
unnamed: R80.1, R81.2, U19.3 (3_VL)
unnamed: J8.2_DIO, M2.38 (SWD_IO)
unnamed: Q8.1 (N_G), U19.6 (6_BATTLO)
unnamed: J8.4_CLK, M2.37 (SWD_CLK)
unnamed: Q8.3 (P_G), Q8.6 (N_D), R82.1
unnamed: R90.2, R91.P$2, U18.P$5 (5_VOUT)
unnamed: M2.18 (P0_30_AIN6), R92.P$1, TP31.P$1
unnamed: G1.P$3 (3_PIN), M2.24 (LORA_TR)
unnamed: LED17.A, R92.P$2
unnamed: C62.1, C63.1, C64.1, J8.1_VREF, M2.15 (VDD), R90.1
unnamed: J8.6_SWO, TP22.P$1
unnamed: C65.1, LED16.A, Q1.3_D (D)
unnamed: PIR2.DL (DIRECT_LINK), U24.P$10 (10_PB6)
NRST: C61.1, J4.3_RST, R88.P$2, SW1.P$2, U$5.25 (NRST)
OSC32_IN: U$5.8 (PC14/OSC32_IN), X2.P$2 (2_OUT)
OSC32_OUT: U$5.9 (PC15/OSC32_OUT)
PI_PWRC: M2.20 (P0_28_AIN4)
QSPI_CLK: U17.6_CL (6_CLK), U$5.22 (PF10/FMC_INTR/DCMI_D11/LCD_DE)
QSPI_CS: U17.1_CS, U$5.91 (PG6/FSMC_INT2/DCMI_D12)
QSPI_D0: U17.5_DI (5_MOSI), U$5.20 (PF8/TIM13_CH1/SPI5_MISO/SAI1_SCK_B/FMC_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)
QSPI_D1: U17.2_DP (2_MISO), U$5.21 (PF9/TIM14_CH1/SPI5_MOSI/SAI1_FS_B/FMC_CD)
QSPI_D2: U17.3_WP, U$5.19 (PF7/TIM11_CH1/SPI5_SCK/SAI1_MCLK_B/UART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)
QSPI_D3: U17.7_RST, U$5.18 (PF6/TIM10_CH1/SPI5_NSS/SAI1_SD_B/UART7_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)
RST_TINY: J5.2_RST_PGM (2_RESET), U24.P$23 (23_PA0_RST), U$5.35 (PA1/USART2_RTS/UART4_RX/TIM5_CH2/TIM2_C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)
RX_FRM_LRW: M2.10 (P0_06), TP32.P$1, U$5.122 (PD6/SPI3_MOSI/I2S3_SD/USART2_RX/FMC_NWA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)
SDIO_CLK: SD1.P5 (P5_CLK), U$5.113 (PC12/UART5_TX/SDIO_CK/DCMI_D9/SPI3_MOSI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)
SDIO_CMD: R66.1, SD1.P2 (P2_CMD), U$5.116 (PD2/TIM3_ETR/UART5_RX/SDIO_CMD/DCMI_D11)
SDIO_D0: R64.1, SD1.P7 (P7_DAT0), U$5.98 (PC8/TIM8_CH3/SDIO_D0/TIM3_CH3/USART6_CK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)
SDIO_D1: R63.1, SD1.P8 (P8_DAT1), U$5.99 (PC9/I2S_CKIN/MCO2/TIM8_CH4/SDIO_D1/I2C3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)
SDIO_D2: R61.1, SD1.P9 (P9_DAT2), U$5.111 (PC10/SPI3_SCK/I2S3_CK/UART4_TX/SDIO_D2/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)
SDIO_D3: R62.1, SD1.P1 (P1_DAT3), U$5.112 (PC11/UART4_RX/SPI3_MISO/SDIO_D3/DCMI_D4)
SDIO_PWRC: IC6.3 (EN), R84.1
SD_CD: SD1.CD, TP23.P$1, U$5.92 (PG7/FSMC_INT3/DCMI_D13)
SENSOR_PWRC: Q5.1_G (G)
SENSPWR: R75.1, R76.1, R77.1, U13.P$2 (2_VDD)
SENS_PWR: C33.1, C34.1, C41.1, J6.P2, Q5.3_D (D), R57.1, R58.1, U6.P$5 (5_VCC), U20.P$5 (5_VDD), U20.P$6 (6_PS)
SPI2_MISO: IR1.P$12 (12_MISO), U$5.75 (PB14/SPI2_MISO/TIM1_CH2N/TIM12_CH1/OTG_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)
SPI2_MOSI: IR1.P$11 (11_MOSI), U$5.76 (PB15/SPI2_MOSI/I2S2_SD/TIM1_CH3N/TIM8_C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)
SPI2_NSS: IR1.P$14 (14_CSL), U$5.73 (PB12/SPI2_NSS/I2S2_WS/I2C2_SMBA/USART3_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)
SPI2_SCLK: IR1.P$13 (13_CLK), U$5.74 (PB13/SPI2_SCK/I2S2_CK/USART3_CTS/TIM1_C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)
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
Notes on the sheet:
1.2K max (for 1.25A chrg curr)
Needed for unprotected LiPos?
ON/OFF SW
ATSAMS7 is 1.7v-3.6v 4.0max
ADJ to GND sets float to 4.0v
VR provides for strong instant pwr-up when connecting to a dead LiPo
2.8v
1.7-3.0v
LCD
Altimeter
BATT
SDcards have absolute max 3.6v
Tie GPS Reset high?
Internal Pullup OK
LBSEL=GND:LBdisconnect at 2.7v
LBSEL=VCC:LBdisconnect at 3.2v
curr
ATWINC: 310mA
ImageSensor: 60mA
Processor: 30mA
gets hot at 4.5ohm
2.65V 3.65V = 370K 517K 113K
VCC Device Power
Host can connect ID pin to gnd
Device can unconnect or connect to ID on uP
OTG connected to ID on uP.
Boot from intern flash when low
3.6v
This can be 5v when batt board is charging.
For Bootloader from USB
Boot1 must be high when doing USB bootloader with Boot0 high.
1554HGYCL 2.3"h Clear
Delete this batt sense stuff?
It's not connected to the batteries!

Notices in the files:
parts and their libraries:
InSight_SiP_ISP4520xx: Copyright (c)2019, All Rights Reserved.
